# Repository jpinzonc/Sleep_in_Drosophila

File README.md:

## DROSOPHILA SLEEP ACTIVITY

Python script designed to estimate the sleep time in Drosophila flies during
an experiment using the Drosophila Activity Monitor (DAM) system. 

# Purpose:
Develop an script that can read and calculate the activity of the flies in the DAM system.

# Estrategy:
The script calculates the sleep numbers on a single monitor file. 

# Usage:

> pyhton sleep.py filename [f/s/a]

Teo parameters are paseed:

 1. - filename is the file produced during the experiment by the DAM system. 
 
 2. one of three analysis options: 
  - f = "final" result, a three column data frame with sample number, and the day and night sleep numbers
 
  - s = "summary" a summary of the sleep data per hour 
 
  - a = "all", both f and s together
 
     The default argunment is f

Example_sleep.txt is a test file, run this command to test

> python sleep.py Example_sleep.txt f

The script was writen in Python 3.6, using pandas (0.23.0), numpy (1.14.3), and os.

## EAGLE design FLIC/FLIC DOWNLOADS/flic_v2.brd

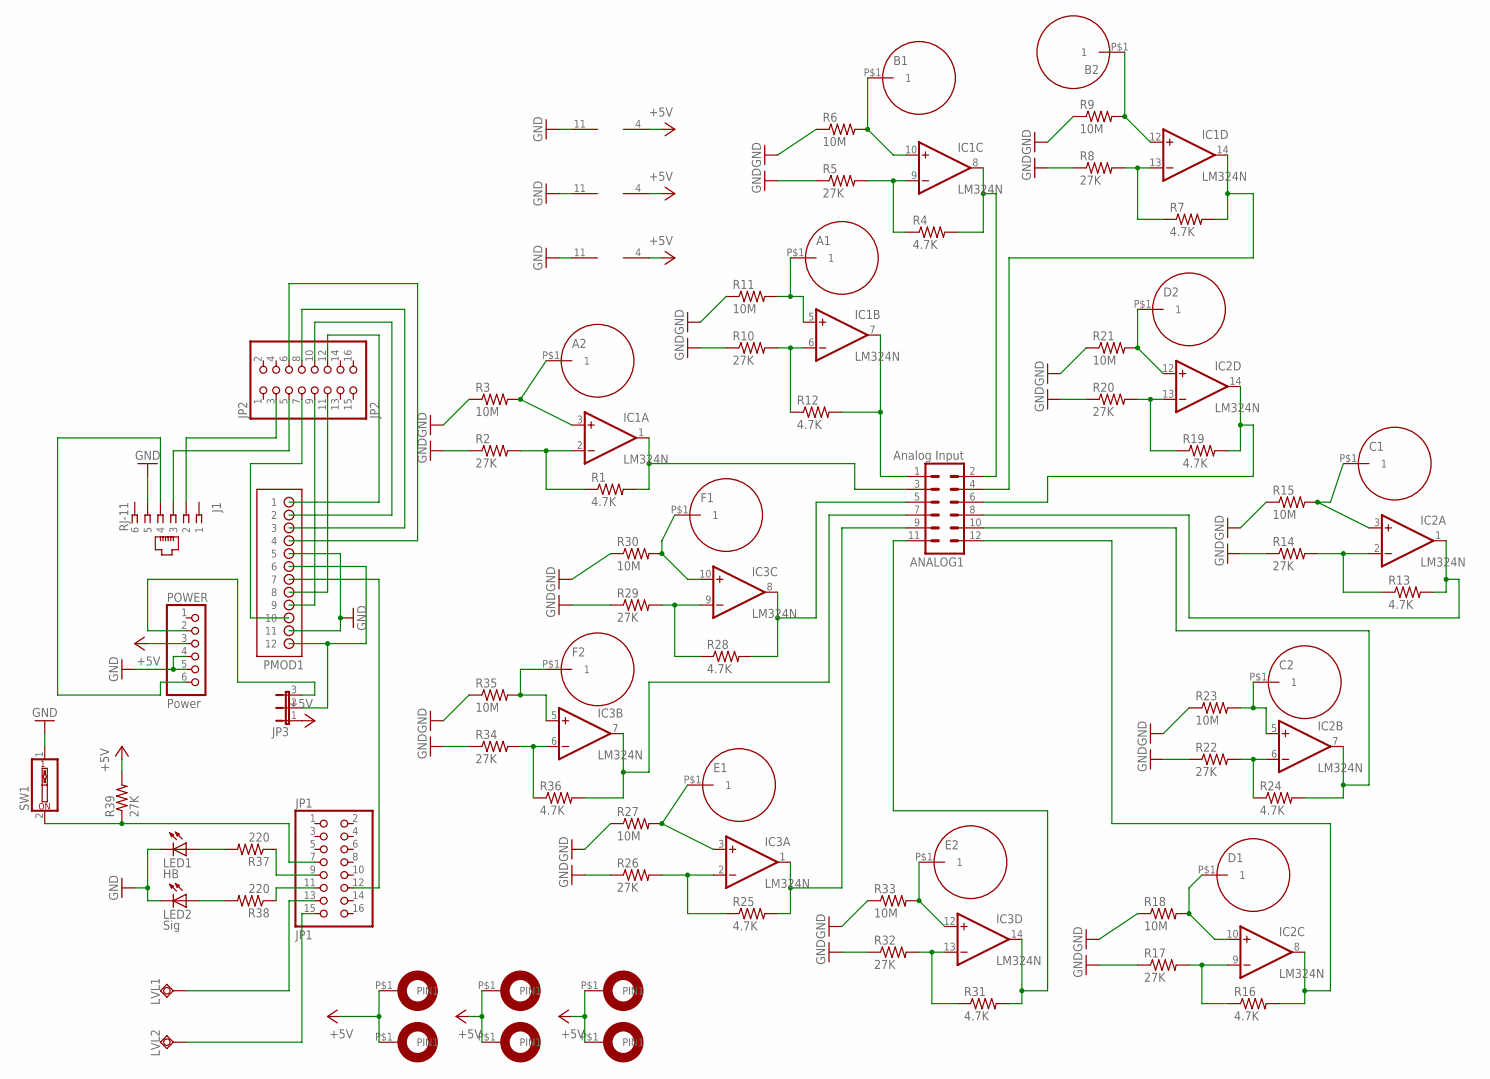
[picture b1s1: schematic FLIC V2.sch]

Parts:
A1, A2: FLIC_PADPAD; FLICPAD
ANALOG1: Analog Input; MA06-2
B1, B2: FLIC_PADPAD; FLICPAD
C1, C2: FLIC_PADPAD; FLICPAD
D1, D2: FLIC_PADPAD; FLICPAD
E1, E2: FLIC_PADPAD; FLICPAD
F1, F2: FLIC_PADPAD; FLICPAD
IC1, IC2, IC3: LM324N; DIL14
J1: RJ-11; RJ11-NO_SHIELD
JP1: JP1; 2X08
JP2: JP2; 2X08
JP3: JP2E; JP2
LED1: HB; LED3MM
LED2: Sig; LED3MM
LVL1, LVL2: TPSQTP20R; TP20R
PMOD1: PMOD-2X6-S
POWER: Power; 1X06
R1, R4, R7, R12, R13, R16, R19, R24, R25, R28, R31, R36: 4.7K; 0207/10
R2, R5, R8, R10, R14, R17, R20, R22, R26, R29, R32, R34, R39: 27K; 0207/10
R3, R6, R9, R11, R15, R18, R21, R23, R27, R30, R33, R35: 10M; 0207/10
R37, R38: 220; 0207/10
SW1: SW_DIP-1; EDG-01
U$1, U$2, U$3, U$4, U$5, U$6: 4MM_HOLEA; 4MM

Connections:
+5V: IC1.4 (V+), IC2.4 (V+), IC3.4 (V+), JP3.1, POWER.3, R39.2, U$1.P$1, U$2.P$1, U$3.P$1, U$4.P$1, U$5.P$1, U$6.P$1
GND: IC1.11 (V-), IC2.11 (V-), IC3.11 (V-), J1.5, LED1.K (C), LED2.K (C), PMOD1.5, PMOD1.11, POWER.4, POWER.5, R2.1, R3.1, R5.1, R6.1, R8.1, R9.1, R10.1, R11.1, R14.1, R15.1, R17.1, R18.1, R20.1, R21.1, R22.1, R23.1, R26.1, R27.1, R29.1, R30.1, R32.1, R33.1, R34.1, R35.1, SW1.1
unnamed: IC1.2 (-IN), R1.1, R2.2
unnamed: A2.P$1, IC1.3 (+IN), R3.2
unnamed: IC1.13 (-IN), R7.1, R8.2
unnamed: A1.P$1, IC1.5 (+IN), R11.2
unnamed: B1.P$1, IC1.10 (+IN), R6.2
unnamed: IC2.2 (-IN), R13.1, R14.2
unnamed: C1.P$1, IC2.3 (+IN), R15.2
unnamed: B2.P$1, IC1.12 (+IN), R9.2
unnamed: ANALOG1.4, IC1.14 (OUT), R7.2
unnamed: IC1.6 (-IN), R10.2, R12.1
unnamed: JP2.10, PMOD1.2
unnamed: D1.P$1, IC2.10 (+IN), R18.2
unnamed: IC1.9 (-IN), R4.1, R5.2
unnamed: ANALOG1.3, IC1.1 (OUT), R1.2
unnamed: ANALOG1.1, IC1.7 (OUT), R12.2
unnamed: D2.P$1, IC2.12 (+IN), R21.2
unnamed: ANALOG1.6, IC2.14 (OUT), R19.2
unnamed: IC2.6 (-IN), R22.2, R24.1
unnamed: IC2.9 (-IN), R16.1, R17.2
unnamed: C2.P$1, IC2.5 (+IN), R23.2
unnamed: IC3.2 (-IN), R25.1, R26.2
unnamed: ANALOG1.12, IC2.8 (OUT), R16.2
unnamed: ANALOG1.10, IC2.7 (OUT), R24.2
unnamed: IC2.13 (-IN), R19.1, R20.2
unnamed: ANALOG1.8, IC2.1 (OUT), R13.2
unnamed: E1.P$1, IC3.3 (+IN), R27.2
unnamed: F1.P$1, IC3.10 (+IN), R30.2
unnamed: E2.P$1, IC3.12 (+IN), R33.2
unnamed: ANALOG1.11, IC3.14 (OUT), R31.2
unnamed: IC3.6 (-IN), R34.2, R36.1
unnamed: IC3.9 (-IN), R28.1, R29.2
unnamed: F2.P$1, IC3.5 (+IN), R35.2
unnamed: ANALOG1.5, IC3.8 (OUT), R28.2
unnamed: ANALOG1.7, IC3.7 (OUT), R36.2
unnamed: IC3.13 (-IN), R31.1, R32.2
unnamed: JP2.8, PMOD1.3
unnamed: LED1.A, R37.2
unnamed: LED2.A, R38.2
unnamed: JP1.9, R37.1
unnamed: JP1.11, R38.1
unnamed: JP1.13, LVL1.TP
unnamed: JP1.15, LVL2.TP
unnamed: J1.2, JP2.3
unnamed: J1.3, JP2.5
unnamed: J1.4, POWER.6
unnamed: ANALOG1.9, IC3.1 (OUT), R25.2
unnamed: JP2.6, PMOD1.4
unnamed: ANALOG1.2, IC1.8 (OUT), R4.2
unnamed: JP1.12, PMOD1.7
unnamed: JP2.11, PMOD1.8
unnamed: JP2.9, PMOD1.9
unnamed: JP2.12, PMOD1.1
unnamed: JP2.7, PMOD1.10
unnamed: JP3.2, PMOD1.6, PMOD1.12
unnamed: JP3.3, POWER.2
unnamed: JP1.7, R39.1, SW1.2

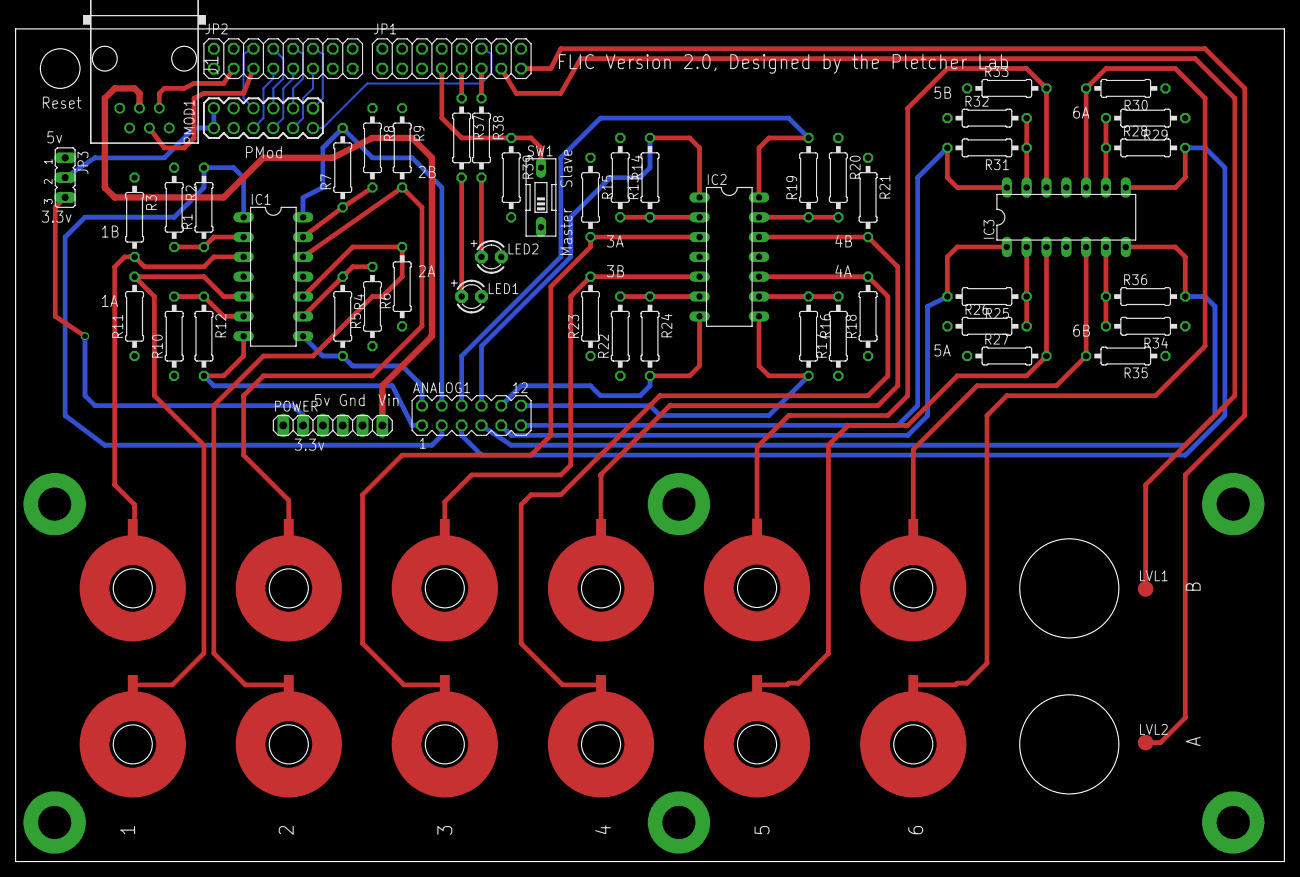
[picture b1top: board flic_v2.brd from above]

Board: 4 copper layers, 162.6 x 108.4 mm, 72 parts (0 on the bottom side), 58 nets.

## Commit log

2017-11-07 initial upload
2018-09-08 CODE: Cleaning the functions
2020-12-22 possible changes
2020-12-22 Additional
    Other Drosophila projects.
2020-12-22 FLIC
    Adding FLIC code and data
